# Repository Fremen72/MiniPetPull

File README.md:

# MiniPetPull
Recycler PET plastic bottles into filament for 3D printer

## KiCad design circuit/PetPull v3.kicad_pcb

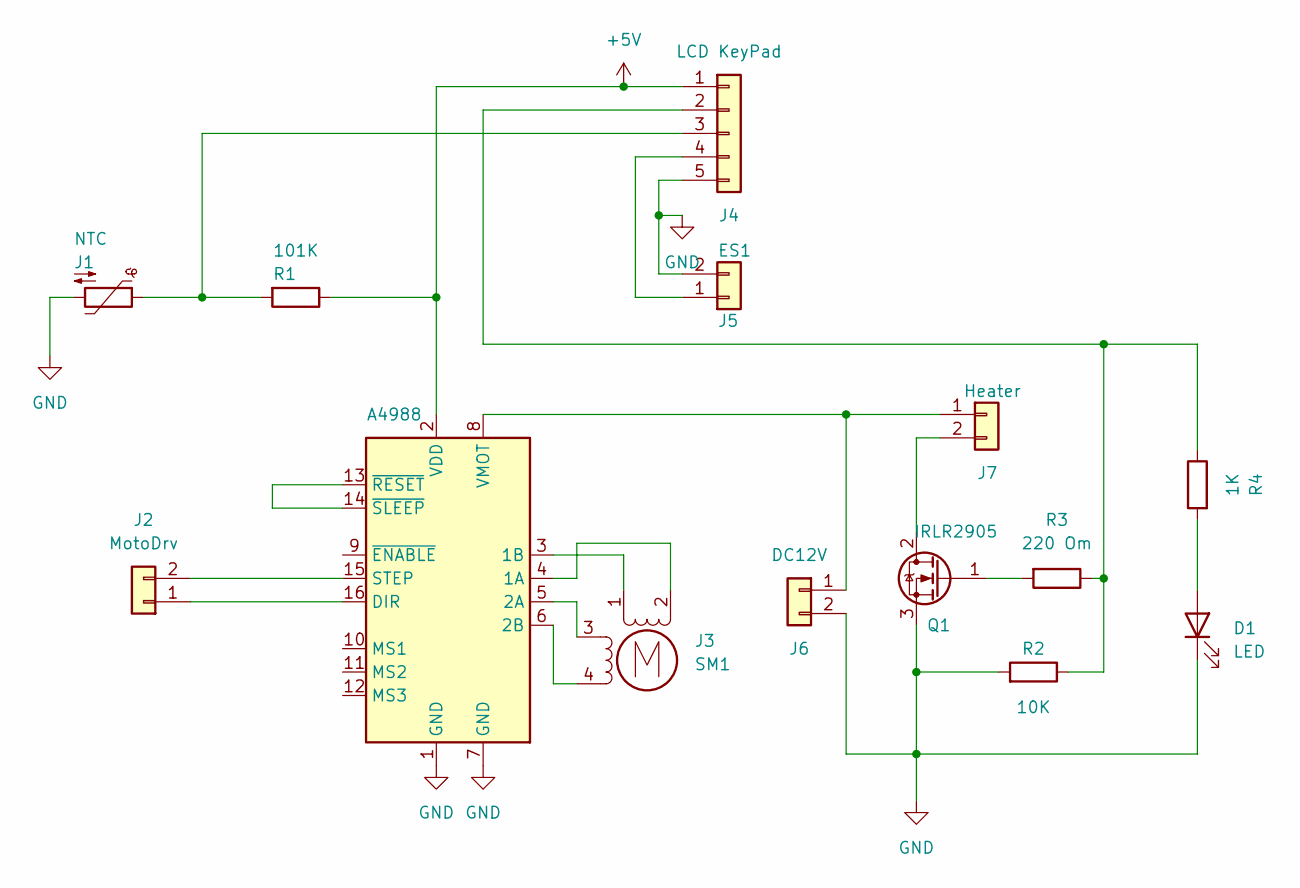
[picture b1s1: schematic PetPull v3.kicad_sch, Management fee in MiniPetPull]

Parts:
A1: A4988; Pololu_Breakout-16_15.2x20.3mm
D1: LED; LED_D3.0mm
J1: NTC; TerminalBlock_TE_282834-2_1x02_P2.54mm_Horizontal
J2: MotoDrv; PinSocket_1x02_P2.54mm_Vertical
J3: SM1; TerminalBlock_TE_282834-4_1x04_P2.54mm_Horizontal
J4: LCD KeyPad; PinSocket_1x05_P2.54mm_Vertical
J5: ES1; TerminalBlock_TE_282834-2_1x02_P2.54mm_Horizontal
J6: DC12V; TerminalBlock_bornier-2_P5.08mm
J7: Heater; TerminalBlock_bornier-2_P5.08mm
Q1: IRLR2905; TO-252-2
R1: 101K; R_Axial_DIN0207_L6.3mm_D2.5mm_P10.16mm_Horizontal
R2: 10K; R_Axial_DIN0207_L6.3mm_D2.5mm_P10.16mm_Horizontal
R3: 220 Om; R_Axial_DIN0207_L6.3mm_D2.5mm_P10.16mm_Horizontal
R4: 1K; R_Axial_DIN0207_L6.3mm_D2.5mm_P10.16mm_Horizontal

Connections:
+5V: A1.2 (VDD), J4.1, R1.1
GND: A1.1 (GND), A1.7 (GND), D1.1 (K), J1.2, J4.5, J5.2, J6.2, Q1.3 (S), R2.2
unnamed: A1.4 (1A), J3.2 (-)
unnamed: A1.3 (1B), J3.1
unnamed: A1.5 (2A), J3.3
unnamed: A1.6 (2B), J3.4
unnamed: A1.16 (DIR), J2.1
unnamed: A1.15 (STEP), J2.2
unnamed: A1.8 (VMOT), J6.1, J7.1
unnamed: A1.13 (~RESET), A1.14 (~SLEEP)
unnamed: D1.2 (A), R4.2
unnamed: J4.2, R2.1, R3.1, R4.1
unnamed: J1.1, J4.3, R1.2
unnamed: J4.4, J5.1
unnamed: J7.2, Q1.2 (D)
unnamed: Q1.1 (G), R3.2

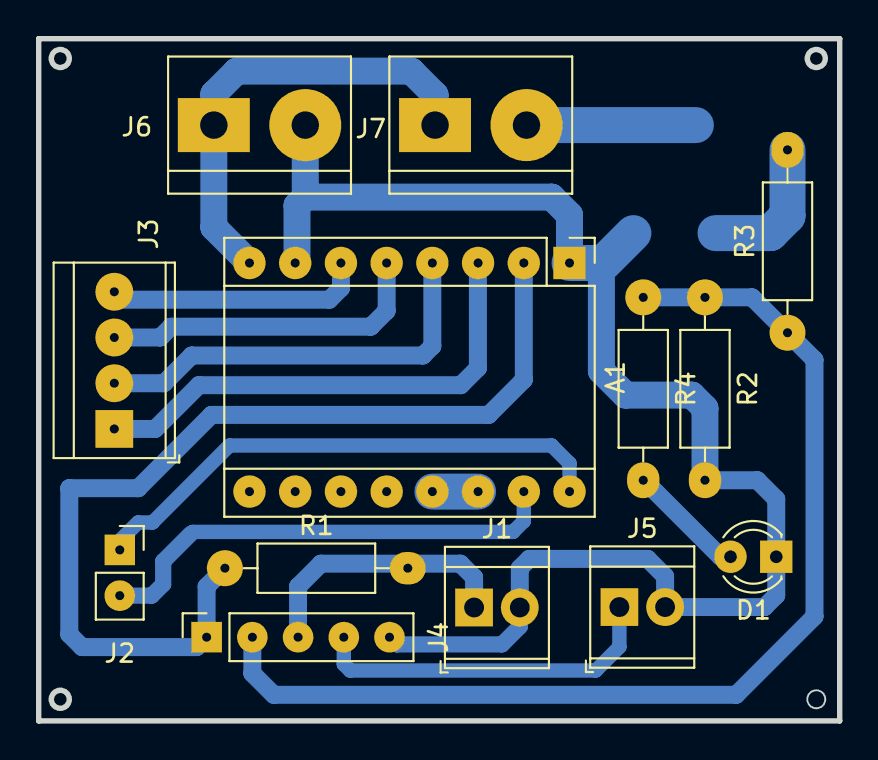
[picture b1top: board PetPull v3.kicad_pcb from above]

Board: 2 copper layers, 44.5 x 37.9 mm, 14 parts (1 on the bottom side), 16 nets.

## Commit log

2024-02-28 Start load firmware MiniPetPull
2024-03-04 Circuit management fee in MiniPetPull
